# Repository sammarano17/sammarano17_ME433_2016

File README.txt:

Files for ME433

4-1-16

a new line

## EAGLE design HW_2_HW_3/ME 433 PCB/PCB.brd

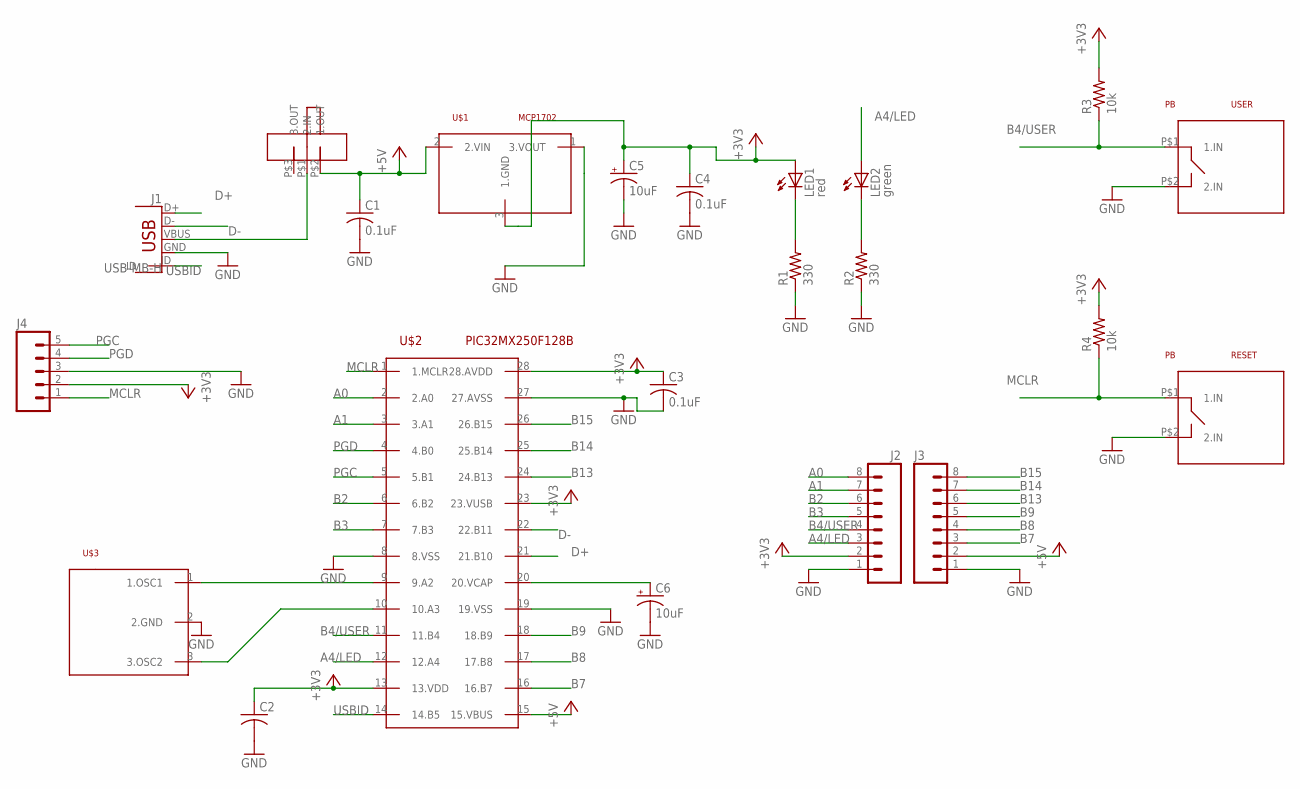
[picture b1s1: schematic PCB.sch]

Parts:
C1, C3, C4: 0.1uF; C025-025X050
C2: C-US025-025X050; C025-025X050
C5, C6: 10uF; B45181A
J1: USB-MB-H
J2, J3: M08; 1X08_ROUND
J4: M05PTH; 1X05
LED1: red; LED3MM
LED2: green; LED3MM
R1, R2: 330; 0207/10
R3, R4: 10k; 0207/10
RESET: PB; PUSHBUTTON
U$1: MCP1702; TO92
U$2: PIC32MX250F128B; DIL28-3
U$3: CRES; 1X03
U$5: SLIDE
USER: PB; PUSHBUTTON

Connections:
+3V3: C2.1, C3.1, C4.1, C5.+, J2.2, J4.2, LED1.A, R3.2, R4.2, U$1.3 (1.GND), U$2.13 (13.VDD), U$2.23 (23.VUSB), U$2.28 (28.AVDD)
+5V: C1.1, J3.2, U$1.2 (2.VIN), U$2.15 (15.VBUS), U$5.P$2 (1.OUT)
A0: J2.8, U$2.2 (2.A0)
A1: J2.7, U$2.3 (3.A1)
A4/LED: J2.3, LED2.A, U$2.12 (12.A4)
B2: J2.6, U$2.6 (6.B2)
B3: J2.5, U$2.7 (7.B3)
B4/USER: J2.4, R3.1, U$2.11 (11.B4), USER.P$1 (1.IN)
B7: J3.3, U$2.16 (16.B7)
B8: J3.4, U$2.17 (17.B8)
B9: J3.5, U$2.18 (18.B9)
B13: J3.6, U$2.24 (24.B13)
B14: J3.7, U$2.25 (25.B14)
B15: J3.8, U$2.26 (26.B15)
D+: J1.D+, U$2.21 (21.B10)
D-: J1.D-, U$2.22 (22.B11)
GND: C1.2, C2.2, C3.2, C4.2, C5.-, C6.-, J1.GND, J2.1, J3.1, J4.3, R1.1, R2.1, RESET.P$2 (2.IN), U$1.1 (3.VOUT), U$2.8 (8.VSS), U$2.19 (19.VSS), U$2.27 (27.AVSS), U$3.2 (2.GND), USER.P$2 (2.IN)
MCLR: J4.1, R4.1, RESET.P$1 (1.IN), U$2.1 (1.MCLR)
unnamed: J1.VBUS, U$5.P$1 (2.IN)
unnamed: LED2.K (C), R2.2
unnamed: LED1.K (C), R1.2
unnamed: C6.+, U$2.20 (20.VCAP)
unnamed: U$2.10 (10.A3), U$3.3 (3.OSC2)
unnamed: U$2.9 (9.A2), U$3.1 (1.OSC1)
PGC: J4.5, U$2.5 (5.B1)
PGD: J4.4, U$2.4 (4.B0)
USBID: J1.ID, U$2.14 (14.B5)

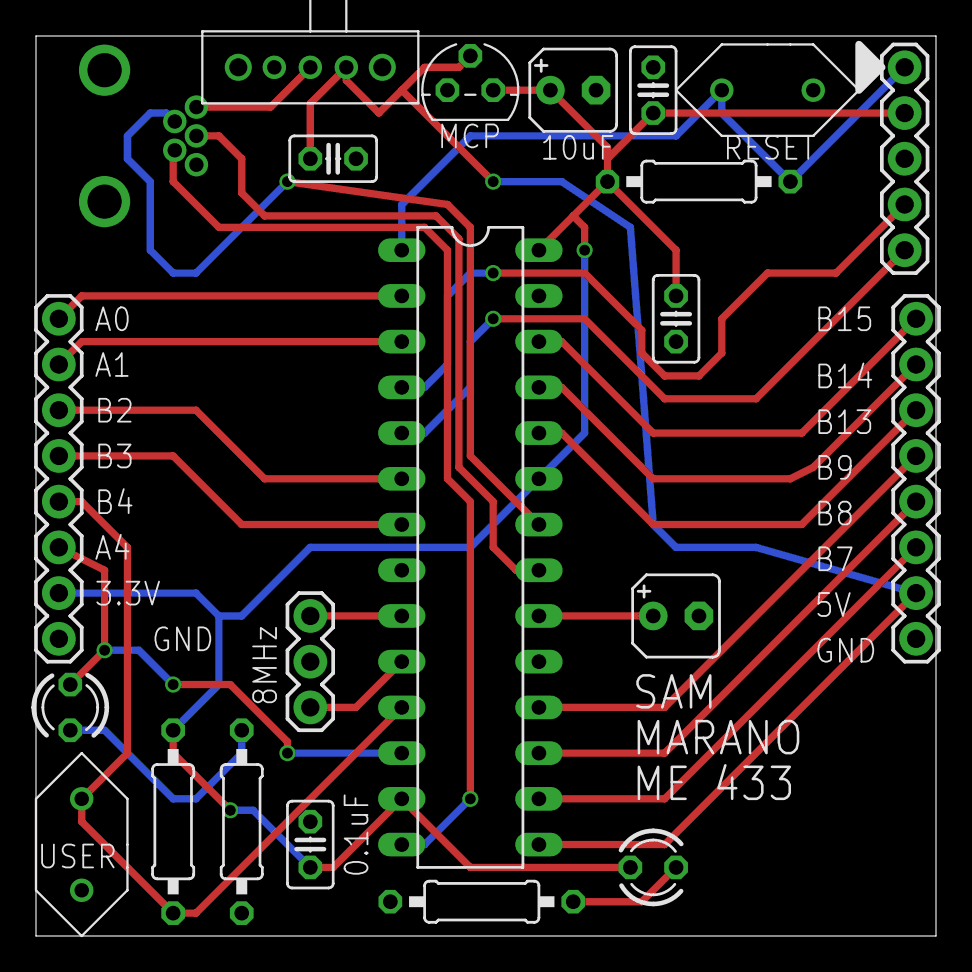
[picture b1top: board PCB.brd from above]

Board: 2 copper layers, 50.0 x 50.0 mm, 22 parts (0 on the bottom side), 27 nets.

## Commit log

2016-04-01 :neckbeard: Added .gitattributes & .gitignore files
2016-04-01 my first commit
2016-04-01 a new line
2016-04-05 Oscillations w/o caps
2016-04-05 HW1 pictures
2016-04-06 HW_1 initial files
2016-04-06 HW_1 loaded
2016-04-08 HW_1 update
2016-04-13 HW 2 Update
2016-04-13 HW2 update
2016-04-14 Ready to be checked before order
2016-04-30 HW_4 update
2016-04-30 HW4 Updates
2016-05-01 HW_6 update
2016-05-02 HW_6 debugging
2016-05-04 HW_5 beginning
2016-05-05 HW_5 updates
2016-05-05 HW_5 working
2016-05-05 HW_5 done
2016-05-05 Updates to HW_5
2016-05-06 HW_6 updates
2016-05-06 IMU outputting to LCD
2016-05-06 Picture
2016-05-09 USB Mouse progress
2016-05-13 Various updates
2016-05-13 Accelerometer mouse working
2016-06-07 Upload of all Android and Harmony projects
2016-06-08 HW_16 updates
